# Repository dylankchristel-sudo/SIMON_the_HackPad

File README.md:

# SIMOND 

SIMOND is a keypad designed to be usable in several applications. It has 5 keys, a rotary encoder, an OLED display, and 4 WS2812B LEDs. It uses KMK firmware.

# Features:

128x32 OLED Display  
EC11 Rotary encoder  
4 WS2812B AR LEDs

# CAD Model:

Two parts: a case and a lid. (IDK why my PCB rendered that way). The holes will be covered with keycaps and the rotary encoder.

Made in Onshape

# PCB:

The microcontroller is actually a seeed studio XIAO rp2040. For some reason the symbol for that part was labeled wrong on the schematic and PCB editor.

Schematic  

PCB

# Firmware:

 The keys are linked to d, y, l, rgb control, and n.
  The rotary encoder controls volume (up/doen/mute)
  The OLED displays a welcome message aad layer info.
  The LEDs light up for style

# BOM:

4x Cherry MX Switches

* 5x DSA Keycaps  
* 4X M3x12mm SHCS Bolts  
* 4x WS2812B LEDs  
* 1x 0.91" 128x32 OLED Display  
* 1x EC11 Rotary Encoder  
* 1x XIAO RP2040  
* 1x Case

# Extra Stuff

:P

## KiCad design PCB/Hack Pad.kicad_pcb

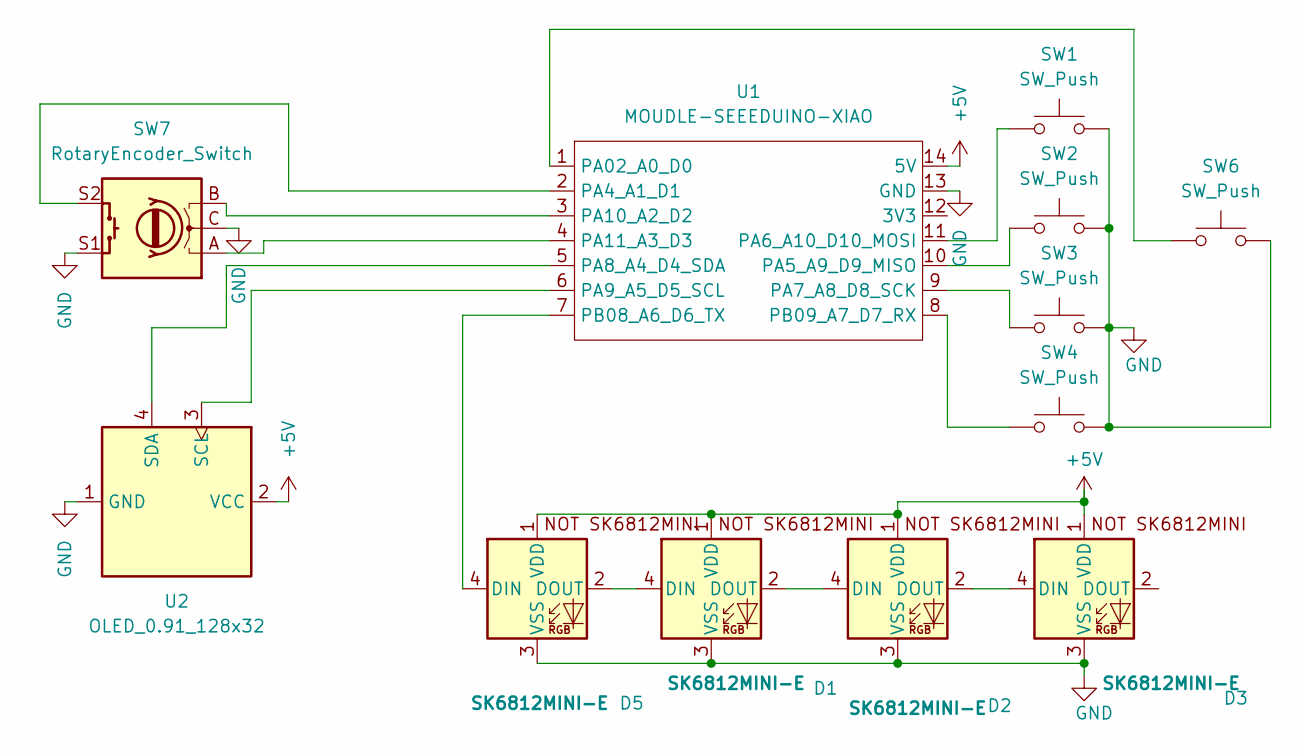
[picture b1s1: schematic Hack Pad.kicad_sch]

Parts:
D1, D2, D3, D5: SK6812MINI-E; SK6812MINI-E_fixed
SW1, SW2, SW3, SW4, SW6: SW_Push; SW_Cherry_MX_1.00u_PCB
SW7: RotaryEncoder_Switch; RotaryEncoder_Alps_EC11E-Switch_Vertical_H20mm
U1: MOUDLE-SEEEDUINO-XIAO; XIAO-Generic-Hybrid-14P-2.54-21X17.8MM
U2: OLED_0.91_128x32; Adafruit_SSD1306

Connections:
+5V: D1.1 (VDD), D2.1 (VDD), D3.1 (VDD), D5.1 (VDD), U1.14 (5V), U2.2 (VCC)
GND: D1.3 (VSS), D2.3 (VSS), D3.3 (VSS), D5.3 (VSS), SW1.2, SW2.2, SW3.2, SW4.2, SW6.2, SW7.C, SW7.S1, U1.13 (GND), U2.1 (GND)
unnamed: D1.4 (DIN), D5.2 (DOUT)
unnamed: D1.2 (DOUT), D2.4 (DIN)
unnamed: D2.2 (DOUT), D3.4 (DIN)
unnamed: D5.4 (DIN), U1.7 (PB08_A6_D6_TX)
unnamed: SW6.1, U1.1 (PA02_A0_D0)
unnamed: SW7.S2, U1.2 (PA4_A1_D1)
unnamed: SW2.1, U1.10 (PA5_A9_D9_MISO)
unnamed: SW1.1, U1.11 (PA6_A10_D10_MOSI)
unnamed: SW3.1, U1.9 (PA7_A8_D8_SCK)
unnamed: U1.5 (PA8_A4_D4_SDA), U2.4 (SDA)
unnamed: U1.6 (PA9_A5_D5_SCL), U2.3 (SCL)
unnamed: SW7.B, U1.3 (PA10_A2_D2)
unnamed: SW7.A, U1.4 (PA11_A3_D3)
unnamed: SW4.1, U1.8 (PB09_A7_D7_RX)

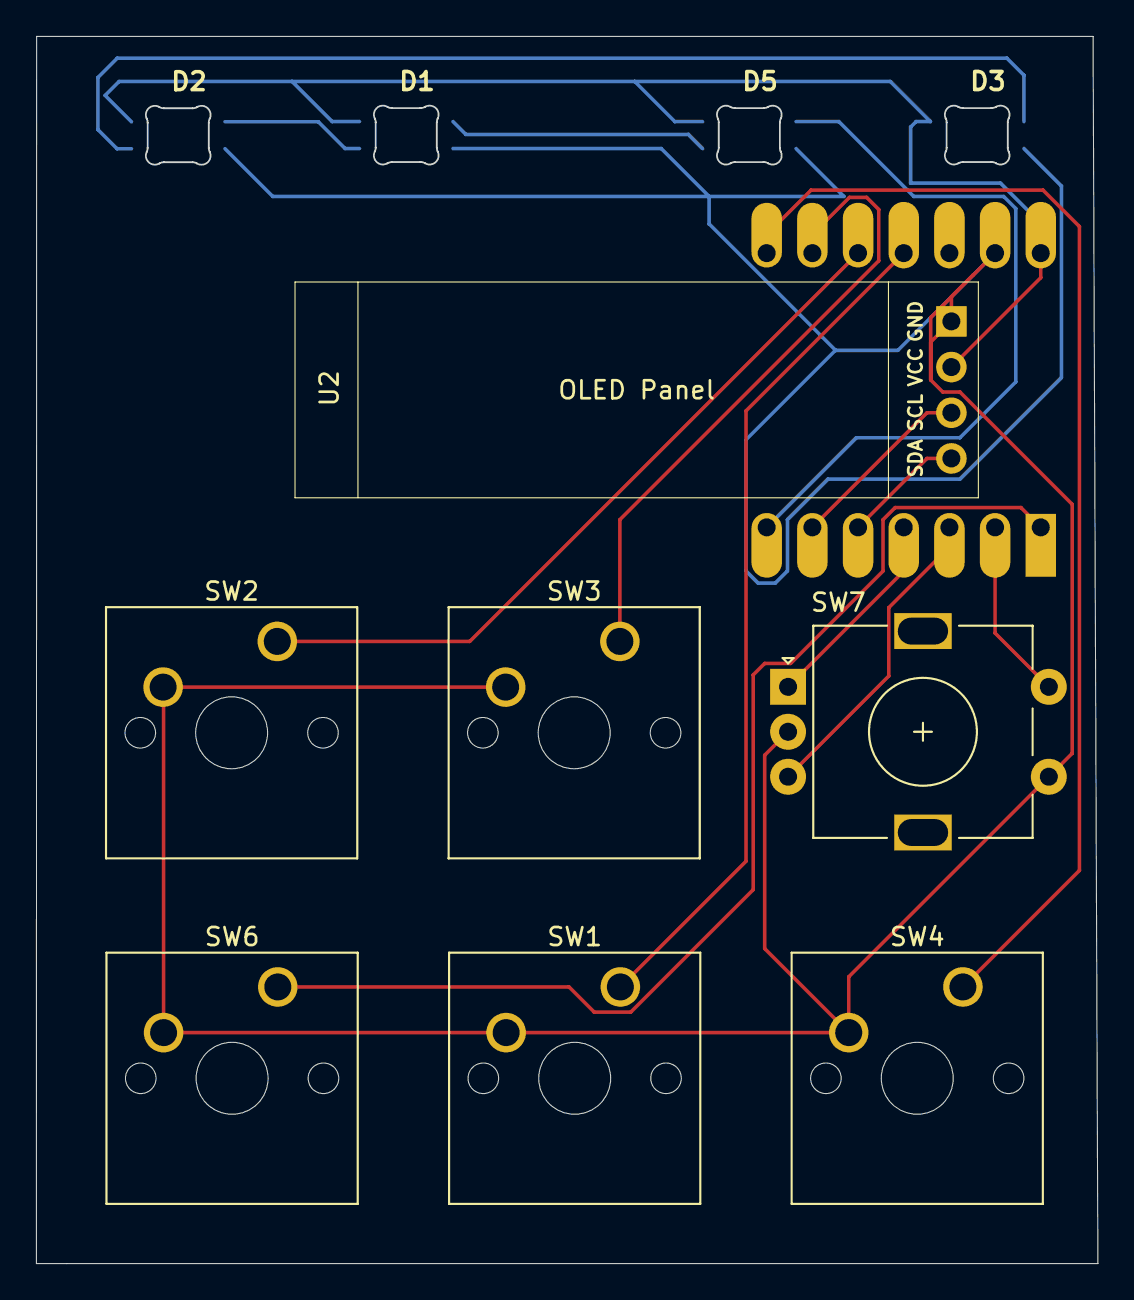
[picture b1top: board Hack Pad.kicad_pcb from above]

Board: 2 copper layers, 59.0 x 68.2 mm, 12 parts (1 on the bottom side), 16 nets.

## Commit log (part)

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2026-03-28 README.md
2026-06-12 Specified firmware section in README
    Clarified firmware description.
2026-06-20 Add project journal detailing development steps
    Documented the steps taken in the project, including setup, schematic design, PCB editing, case design, assembly, and firmware development.
2026-06-24 Fixed spelling for Simond
2026-06-24 Updated firmware in readme.md
2026-06-26 changed pin names on firmware
2026-06-27 Added note about micro controller in readme.md
    Explained discrepancy in part name
2026-06-28 Added image to readme.md
2026-06-28 Flipped image right side up
